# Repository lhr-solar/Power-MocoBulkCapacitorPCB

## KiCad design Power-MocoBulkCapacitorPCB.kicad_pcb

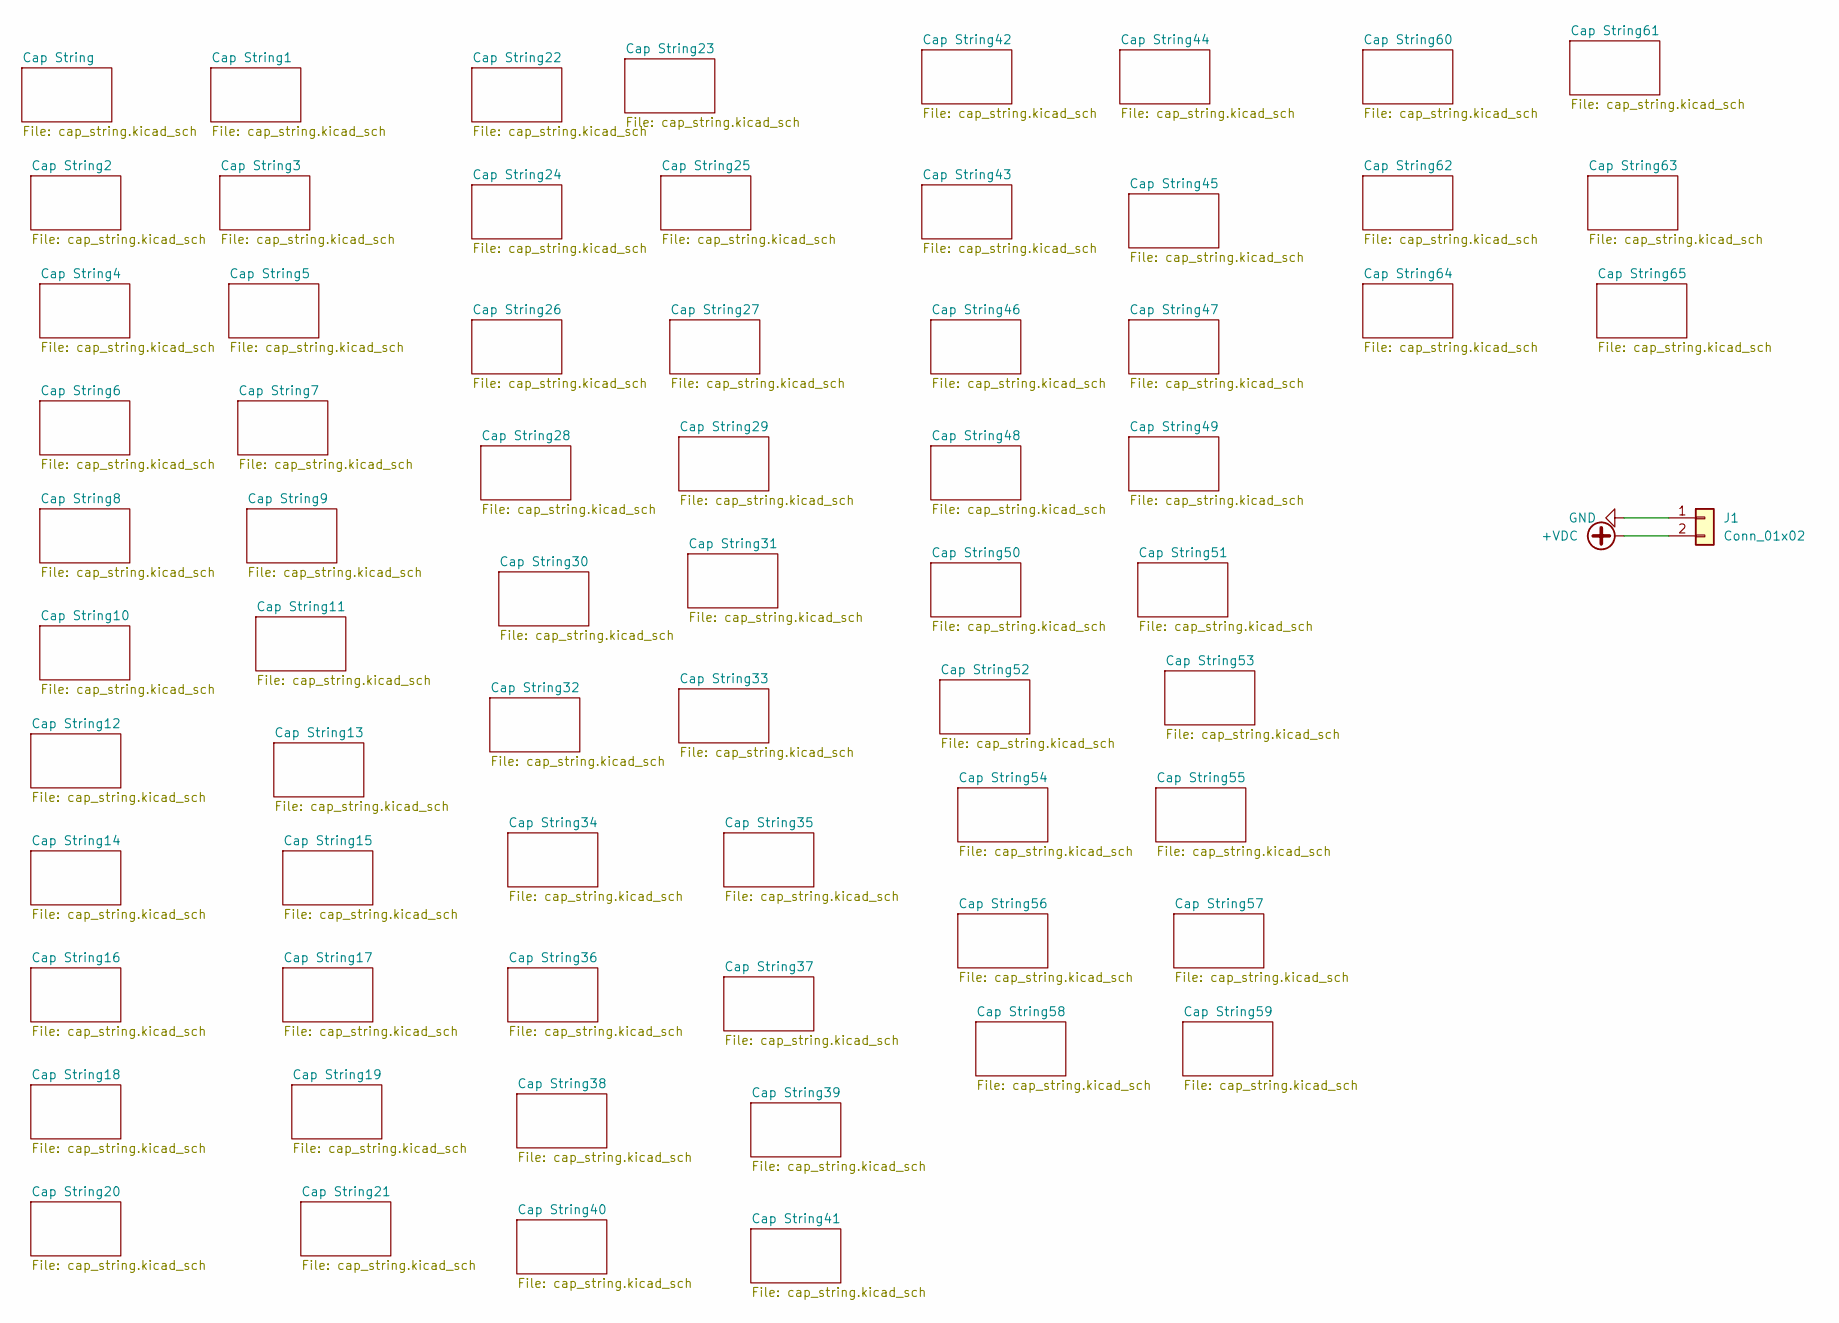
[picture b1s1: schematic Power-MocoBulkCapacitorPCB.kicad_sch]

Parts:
J1: Conn_01x02; AMASS_XT30PW-M_1x02_P2.50mm_Horizontal

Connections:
+VDC: J1.2; also elsewhere on the board
GND: J1.1; also elsewhere on the board

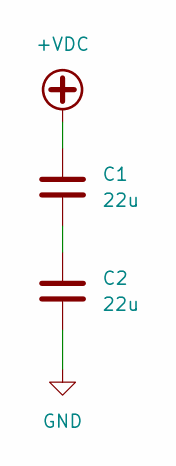
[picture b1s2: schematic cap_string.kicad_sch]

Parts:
C1, C2: 22u; C_2220_5750Metric

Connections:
+VDC: C1.1; also elsewhere on the board
GND: C2.2; also elsewhere on the board
unnamed: C1.2, C2.1

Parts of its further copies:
C3, C4, C5, C6, C7, C8, C9, C10, C11, C12, C13, C14, C15, C16, C17, C18, C19, C20, C21, C22, C23, C24, C25, C26, C27, C28, C29, C30, C31, C32, C33, C34, C35, C36, C37, C38, C39, C40, C41, C42, C43, C44, C45, C46, C47, C48, C49, C50, C51, C52, C53, C54, C55, C56, C57, C58, C59, C60, C61, C62, C63, C64, C65, C66, C67, C68, C69, C70, C71, C72, C73, C74, C75, C76, C77, C78, C79, C80, C81, C82, C83, C84, C85, C86, C87, C88, C89, C90, C91, C92, C93, C94, C95, C96, C97, C98, C99, C100, C101, C102, C103, C104, C105, C106, C107, C108, C109, C110, C111, C112, C113, C114, C115, C116, C117, C118, C119, C120, C121, C122, C123, C124, C125, C126, C127, C128, C129, C130, C131, C132: 22u; C_2220_5750Metric

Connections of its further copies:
+VDC: C3.1, C5.1, C7.1, C9.1, C11.1, C13.1, C15.1, C17.1, C19.1, C21.1, C23.1, C25.1, C27.1, C29.1, C31.1, C33.1, C35.1, C37.1, C39.1, C41.1, C43.1, C45.1, C47.1, C49.1, C51.1, C53.1, C55.1, C57.1, C59.1, C61.1, C63.1, C65.1, C67.1, C69.1, C71.1, C73.1, C75.1, C77.1, C79.1, C81.1, C83.1, C85.1, C87.1, C89.1, C91.1, C93.1, C95.1, C97.1, C99.1, C101.1, C103.1, C105.1, C107.1, C109.1, C111.1, C113.1, C115.1, C117.1, C119.1, C121.1, C123.1, C125.1, C127.1, C129.1, C131.1; also elsewhere on the board
GND: C4.2, C6.2, C8.2, C10.2, C12.2, C14.2, C16.2, C18.2, C20.2, C22.2, C24.2, C26.2, C28.2, C30.2, C32.2, C34.2, C36.2, C38.2, C40.2, C42.2, C44.2, C46.2, C48.2, C50.2, C52.2, C54.2, C56.2, C58.2, C60.2, C62.2, C64.2, C66.2, C68.2, C70.2, C72.2, C74.2, C76.2, C78.2, C80.2, C82.2, C84.2, C86.2, C88.2, C90.2, C92.2, C94.2, C96.2, C98.2, C100.2, C102.2, C104.2, C106.2, C108.2, C110.2, C112.2, C114.2, C116.2, C118.2, C120.2, C122.2, C124.2, C126.2, C128.2, C130.2, C132.2; also elsewhere on the board
unnamed: C3.2, C4.1
unnamed: C5.2, C6.1
unnamed: C7.2, C8.1
unnamed: C9.2, C10.1
unnamed: C11.2, C12.1
unnamed: C13.2, C14.1
unnamed: C15.2, C16.1
unnamed: C17.2, C18.1
unnamed: C19.2, C20.1
unnamed: C21.2, C22.1
unnamed: C23.2, C24.1
unnamed: C25.2, C26.1
unnamed: C27.2, C28.1
unnamed: C29.2, C30.1
unnamed: C31.2, C32.1
unnamed: C33.2, C34.1
unnamed: C35.2, C36.1
unnamed: C37.2, C38.1
unnamed: C39.2, C40.1
unnamed: C41.2, C42.1
unnamed: C43.2, C44.1
unnamed: C45.2, C46.1
unnamed: C47.2, C48.1
unnamed: C49.2, C50.1
unnamed: C51.2, C52.1
unnamed: C53.2, C54.1
unnamed: C55.2, C56.1
unnamed: C57.2, C58.1
unnamed: C59.2, C60.1
unnamed: C61.2, C62.1
unnamed: C63.2, C64.1
unnamed: C65.2, C66.1
unnamed: C67.2, C68.1
unnamed: C69.2, C70.1
unnamed: C71.2, C72.1
unnamed: C73.2, C74.1
unnamed: C75.2, C76.1
unnamed: C77.2, C78.1
unnamed: C79.2, C80.1
unnamed: C81.2, C82.1
unnamed: C83.2, C84.1
unnamed: C85.2, C86.1
unnamed: C87.2, C88.1
unnamed: C89.2, C90.1
unnamed: C91.2, C92.1
unnamed: C93.2, C94.1
unnamed: C95.2, C96.1
unnamed: C97.2, C98.1
unnamed: C99.2, C100.1
unnamed: C101.2, C102.1
unnamed: C103.2, C104.1
unnamed: C105.2, C106.1
unnamed: C107.2, C108.1
unnamed: C109.2, C110.1
unnamed: C111.2, C112.1
unnamed: C113.2, C114.1
unnamed: C115.2, C116.1
unnamed: C117.2, C118.1
unnamed: C119.2, C120.1
unnamed: C121.2, C122.1
unnamed: C123.2, C124.1
unnamed: C125.2, C126.1
unnamed: C127.2, C128.1
unnamed: C129.2, C130.1
unnamed: C131.2, C132.1

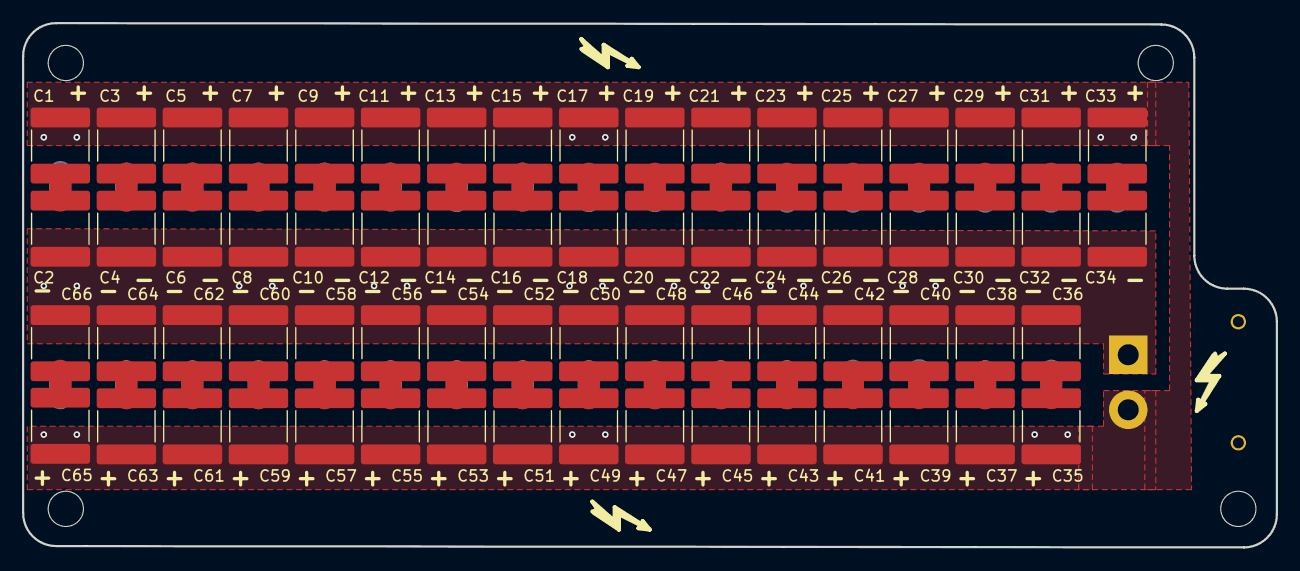
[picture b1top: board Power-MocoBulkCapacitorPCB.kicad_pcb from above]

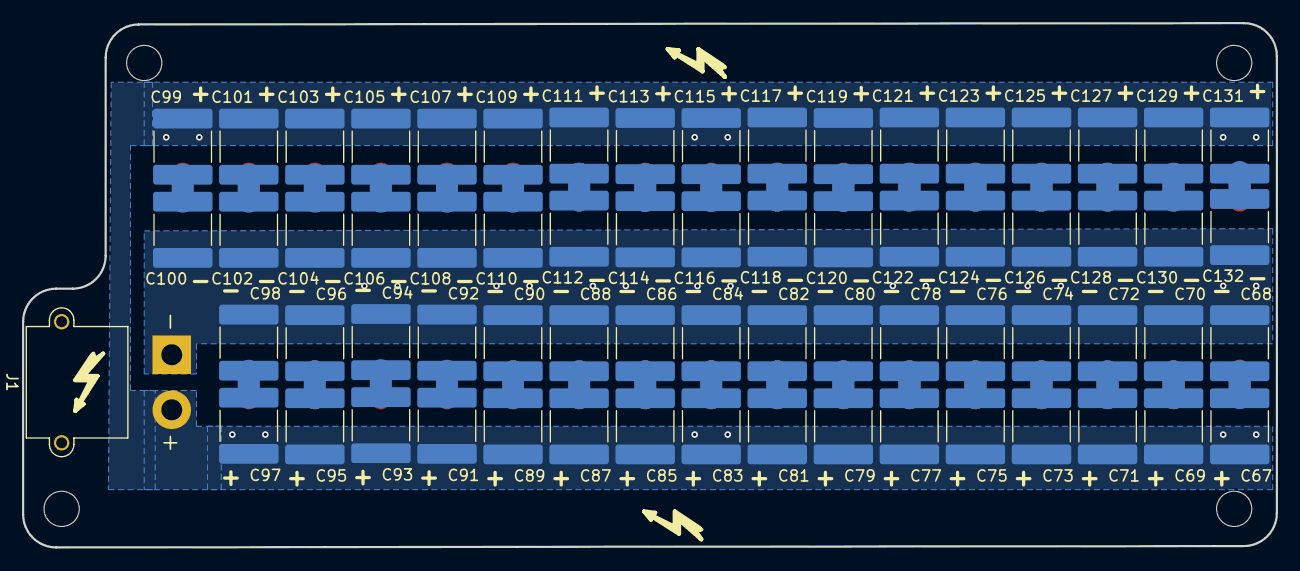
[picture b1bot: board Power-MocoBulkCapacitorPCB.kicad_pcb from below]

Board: 2 copper layers, 113.9 x 47.6 mm, 133 parts (67 on the bottom side), 68 nets.

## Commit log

2025-08-26 holes
2025-08-26 routing
2025-09-09 cap p/n in schem
